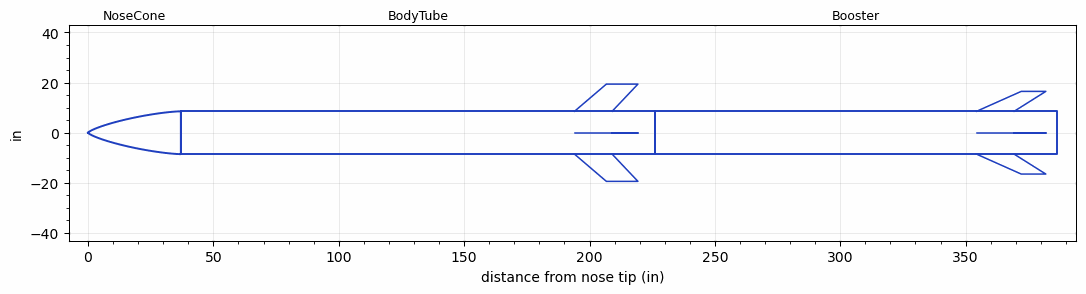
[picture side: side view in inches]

<RASAeroDocument>
 <FileVersion>2</FileVersion>
 <RocketDesign>
  <NoseCone>
   <Length>37.02</Length>
   <Diameter>17.082257</Diameter>
   <Shape>Von Karman Ogive</Shape>
   <Location>0</Location>
  </NoseCone>
  <BodyTube>
   <Length>188.99908</Length>
   <Diameter>17.082257</Diameter>
   <Location>37.02</Location>
   <Fin>
    <Count>4</Count>
    <Chord>15</Chord>
    <Span>10.851821</Span>
    <SweepDistance>12.692724</SweepDistance>
    <TipChord>12.592549</TipChord>
    <Thickness>0.5</Thickness>
    <LERadius>0.5</LERadius>
    <Location>32</Location>
    <AirfoilSection>Double Wedge</AirfoilSection>
    <FX1>1</FX1>
    <FX3>1</FX3>
   </Fin>
  </BodyTube>
  <Booster>
   <Length>160.327944</Length>
   <Diameter>17.082257</Diameter>
   <InsideDiameter>6.17</InsideDiameter>
   <Location>226.01908</Location>
   <ShoulderLength>0</ShoulderLength>
   <Fin>
    <Count>4</Count>
    <Chord>15</Chord>
    <Span>7.9417451</Span>
    <SweepDistance>17.819818</SweepDistance>
    <TipChord>9.8056505</TipChord>
    <Thickness>0.5</Thickness>
    <LERadius>0.5</LERadius>
    <Location>32</Location>
    <AirfoilSection>Double Wedge</AirfoilSection>
    <FX1>1</FX1>
    <FX3>1</FX3>
   </Fin>
  </Booster>
  <Surface>Smooth (Zero Roughness)</Surface>
  <ModifiedBarrowman>False</ModifiedBarrowman>
  <Turbulence>False</Turbulence>
  <UseBooster1>False</UseBooster1>
  <UseBooster2>False</UseBooster2>
 </RocketDesign>
 <LaunchSite>
  <Altitude>2050</Altitude>
  <Pressure>0</Pressure>
  <RodAngle>0</RodAngle>
  <RodLength>24</RodLength>
  <Temperature>90</Temperature>
  <WindSpeed>0</WindSpeed>
 </LaunchSite>
 <Recovery>
  <Altitude1>1000</Altitude1>
  <Altitude2>1000</Altitude2>
  <DeviceType1>Parachute</DeviceType1>
  <DeviceType2>None</DeviceType2>
  <Event1>True</Event1>
  <Event2>False</Event2>
  <Size1>48</Size1>
  <Size2>1</Size2>
  <EventType1>Apogee</EventType1>
  <EventType2>None</EventType2>
  <CD1>0.97</CD1>
  <CD2>1.33</CD2>
 </Recovery>
 <SimulationList>
  <Simulation>
   <SustainerEngine>TBDPS-21  (GTXR)</SustainerEngine>
   <SustainerLaunchWt>117.9</SustainerLaunchWt>
   <SustainerNozzleDiameter>4.18</SustainerNozzleDiameter>
   <SustainerCG>80.19</SustainerCG>
   <SustainerIgnitionDelay>20</SustainerIgnitionDelay>
   <Booster1Engine>TBDPS-21  (GTXR)</Booster1Engine>
   <Booster1LaunchWt>224.93</Booster1LaunchWt>
   <Booster1SeparationDelay>2</Booster1SeparationDelay>
   <Booster1IgnitionDelay>0</Booster1IgnitionDelay>
   <Booster1CG>120.83</Booster1CG>
   <Booster1NozzleDiameter>4.18</Booster1NozzleDiameter>
   <IncludeBooster1>True</IncludeBooster1>
   <Booster2Delay>0</Booster2Delay>
   <IncludeBooster2>False</IncludeBooster2>
   <TimetoApogee>107.1723</TimetoApogee>
   <MaxAltitude>117556.6</MaxAltitude>
   <MaxVelocity>3034.942</MaxVelocity>
   <OptimumWt>81.71671</OptimumWt>
   <OptimumMaxAlt>81.71671</OptimumMaxAlt>
  </Simulation>
 </SimulationList>
</RASAeroDocument>
